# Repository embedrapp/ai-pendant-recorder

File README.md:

# AI Pendant Recorder

An open-source, privacy-first wearable audio recorder built around the Seeed XIAO ESP32S3. It records PDM microphone audio to removable microSD storage and uses a 5 × 5 RGB matrix for low-power status feedback.

## Hardware

- Seeed XIAO ESP32S3 **113991114** controller
- Infineon IM69D130 PDM microphone
- Molex 104031-0811 microSD socket
- MAX17048 fuel gauge and BMI270 IMU
- Regulated haptic output
- 25 × WS2812C-2020-V1 RGB LEDs
- Protected 500 mAh 1S LiPo design target
- No camera or speaker

## Schematics

The schematic is generated from [`pcb/ai_pendant_recorder.zen`](pcb/ai_pendant_recorder.zen) and is organized into battery/fuel-gauge, controller, motion, microphone, storage, haptics, LED power, and LED-row sections. Open the image for the full-resolution view.

## Board

The current four-layer KiCad board is in [`pcb/layout/layout.kicad_pcb`](pcb/layout/layout.kicad_pcb). It has a closed 36 × 76 mm rounded outline, four mounting holes, 115 footprints, 1,264 track segments, 200 vias, and no reported airwires.

Fresh checks on the current board:

| Check | Result |
|---|---|
| Zener source build | Pass — 115 components |
| ERC | Pass — 0 errors, 0 warnings, 79 style advice |
| KiCad DRC | **1 error**, 115 footprint-library configuration warnings |
| PDK-backed DFM | Pass — 0 findings |
| Firmware clean build | Pass for `seeed_xiao_esp32s3` |
| Enclosure CAD build | Pass — 16 valid solids |

The remaining DRC error is a 0.21 mm clearance between the IM69D130 acoustic opening and its surrounding ground pad, below the board-wide 0.25 mm hole-clearance rule. The geometry follows Infineon's recommended 0.8 mm sound port and SMD ground-pad land pattern, but the exception still needs an explicit KiCad rule or footprint-level resolution before the PCB checks are fully clean. The library warnings are caused by the standalone KiCad checker not loading the project-managed footprint libraries; they are not geometry violations.

## Mechanical design

### Pendant enclosure

The parametric enclosure includes a rounded two-part shell, front optical area,
record-button opening, side controls/access, and lanyard loop. The latest STEP
build contains 16 valid solids and measures 40 × 87.785 × 18.2 mm overall,
including the loop.

### Populated PCB model

The populated-board model is used to coordinate PCB and enclosure geometry.
Some component models and exact interface heights remain incomplete, so the
render is a design aid rather than proof of interference-free physical fit.

## Firmware

The Arduino/PlatformIO firmware currently provides:

- push-to-toggle 16-bit PDM audio capture;
- chunked WAV recording to FAT32 microSD;
- recovery of interrupted `.part` recordings at startup; and
- conservative idle/recording animations on the RGB matrix.

Wi-Fi upload, fuel-gauge monitoring, motor activation, and automatic file deletion are not implemented.

### Build

1. Install [PlatformIO](https://platformio.org/).
2. Clone this repository and enter it.
3. Build the default environment:

   ```sh
   pio run
   ```

4. Connect a Seeed XIAO ESP32S3 and upload:

   ```sh
   pio run --target upload
   pio device monitor --baud 115200
   ```

Use a qualified FAT32 microSD card. Hardware pin assignments are documented in [`docs/current-design.md`](docs/current-design.md); setup notes are in [`docs/setup.md`](docs/setup.md).

## Repository map

| Path | Purpose |
|---|---|
| `src/main.cpp` | Recorder firmware entry point |
| `include/` | Shared firmware configuration and WAV helpers |
| `tests/` | Host-side audio-format test |
| `pcb/ai_pendant_recorder.zen` | Electrical and connectivity source |
| `pcb/layout/` | Current KiCad PCB and schematic |
| `pcb/bom.json` | Structured generated BOM |
| `docs/bom.md` | Human-readable procurement notes |
| `mechanical/` | Parametric enclosure source and current PCB STEP import |

## Engineering status

The current source, PCB, firmware, and enclosure generators are maintained together and were freshly built or checked. Remaining hardware work is tracked in [`docs/current-design.md`](docs/current-design.md), including the microphone DRC rule, power and charging validation, exact motor selection, enclosure interface dimensions, and physical bench testing.

## Contributing

Issues and pull requests are welcome. Keep changes focused, identify the hardware revision they target, and include validation evidence where practical. Do not commit credentials, private recordings, generated build directories, or unreviewed manufacturing outputs.

## License

This project is intended to be open source, but no license file is currently present. Until the maintainers add one, copyright law reserves reuse rights; please open an issue before redistributing or incorporating the design.

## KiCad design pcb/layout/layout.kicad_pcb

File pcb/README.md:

# Electronics workspace

The maintained electrical source is `ai_pendant_recorder.zen`; the current physical board is `layout/layout.kicad_pcb`.

Sourcing metadata is stored in the source `PURCHASE_LINKS` / `DATASHEET_INDEX` maps and the persisted `bom.json` overlay. `bom.csv` is generated and should not be hand-edited.

## Board

- 36 × 76 mm rounded outline
- four copper layers, modeled at 1.62 mm total thickness
- 115 footprints
- 1,264 track segments and 200 vias
- no zones and no reported airwires

The source `Board(...)` points to `layout`, so there is one active board location. Regenerating or synchronizing a routed PCB is a deliberate board mutation; preserve and compare copper before doing so.

## Current checks

- Source build: pass, 115 components.
- ERC: pass, 79 style advice entries.
- DRC: one IM69D130 acoustic-hole/ground-land clearance error plus footprint-library configuration warnings.
- PDK-backed DFM: pass with no findings.

The microphone geometry follows Infineon's recommended 0.8 mm PCB sound port and surrounding solder-mask-defined ground land. Represent that intended geometry with a local KiCad rule or reviewed footprint change; do not weaken the global hole-clearance rule.

The four-layer stackup is a project model rather than a controlled-impedance fabricator stackup. Review boost current loops, trace widths, return paths, and the absence of copper planes before fabrication.

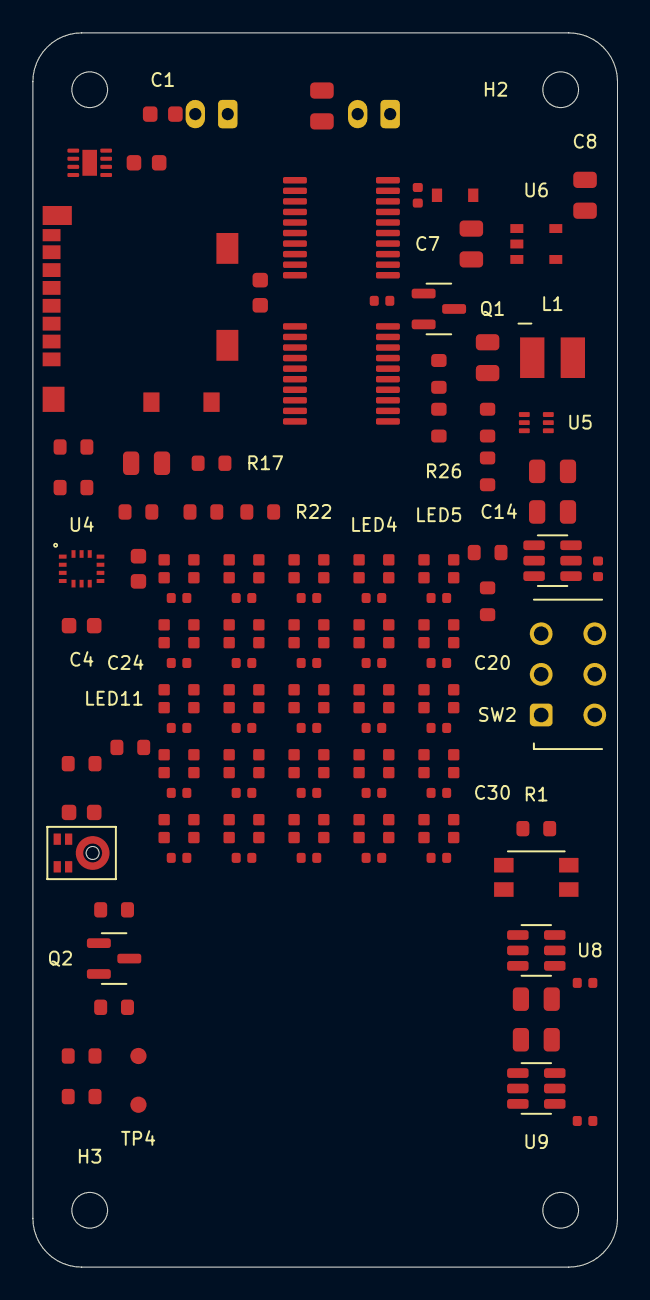
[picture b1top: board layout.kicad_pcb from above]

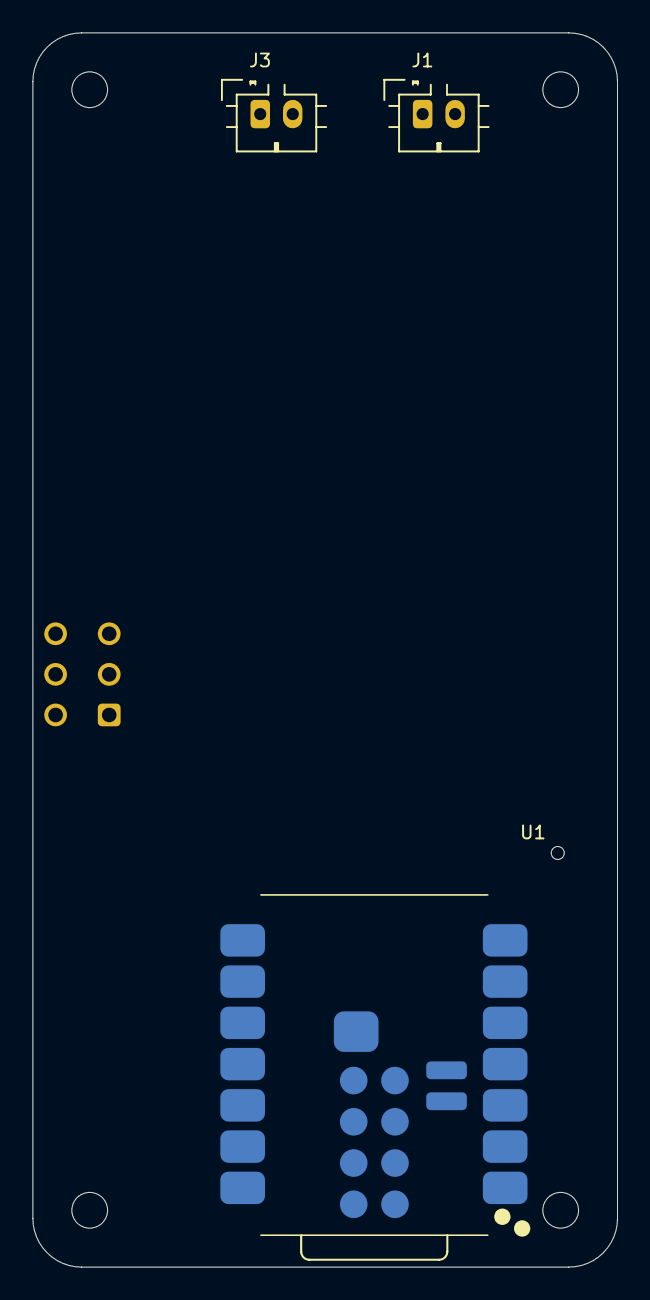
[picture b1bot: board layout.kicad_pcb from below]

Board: 2 copper layers, 36.0 x 76.0 mm, 115 parts (3 on the bottom side), 72 nets, no tracks yet.

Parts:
C1, C3, C4, C5, C9, C10: GCM188R71H104KA57J; C_0603_1608Metric
C2, C7, C8, C11, C12, C43, C44: CC0805KRX5R8BB106; C_0805_2012Metric
C13, C14: GRM21BR61A226ME44L; C_0805_2012Metric
C15, C16, C17, C18, C19, C20, C21, C22, C23, C24, C25, C26, C27, C28, C29, C30, C31, C32, C33, C34, C35, C36, C37, C38, C39, C45, C46: GRM155R71C104KA88D; C_0402_1005Metric
C40, C41, C42: GRM1555C1E102JA01D; C_0402_1005Metric
D1: NSVR0320MW2T1G; NSVR0320
H1, H2, H3, H4: M2 DIN965 Mechanical; MountingHole_2.2mm_M2_DIN965
J1, J3: B2B-PH-K-S; JST_PH_B2B-PH-K_1x02_P2.00mm_Vertical
J4: 104031-0811; Molex_104031-0811
L1: XEL4030-102MEC; XEL4030_102MEC
LED1, LED2, LED3, LED4, LED5, LED6, LED7, LED8, LED9, LED10, LED11, LED12, LED13, LED14, LED15, LED16, LED17, LED18, LED19, LED20, LED21, LED22, LED23, LED24, LED25: WS2812C-2020-V1; WS2812C_2020_V1
MK1: IM69D130V01XTSA1; IM69D130
Q1, Q2: AO3400A; SOT-23
R1, R8, R23, R26, R27, R29: RC0603FR-07100KL; R_0603_1608Metric
R4, R5, R30: RC0603FR-074K7L; R_0603_1608Metric
R7: RC0603FR-07100RL; R_0603_1608Metric
R16, R17: RC0603FR-0733RL; R_0603_1608Metric
R18, R19, R20, R21, R22: RC0603FR-0747KL; R_0603_1608Metric
R25: RC0603FR-07732KL; R_0603_1608Metric
R28: RC0603FR-07470RL; R_0603_1608Metric
SW1: PTS841GKSMTR LFS; PTS841GK
SW2: JS202011AQN; SW_CK_JS202011AQN_DPDT_Angled
TP3, TP4: ?; TestPoint_Pad_D1.0mm
U1: 113991114; XIAO
U3: MAX17048G+T10; kicad_footprint
U4: BMI270
U5: TPS61023DRLR; Texas_R-PDSO-N6_DRL-6
U6: AP2112K-3.3TRG1; AP2112K_3V3
U7, U8, U9: TPS22918DBVR; SOT-23-6
U10, U11: SN74CBTLV3245APWR; TSSOP-20

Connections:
BAT_RISE: C42.1, U9.4
BOOST_5V: C13.1, C14.1, R25.1, U5.6, U7.1
FG_SCL: R5.1, TP4.1, U3.7, U4.13, U10.11
FG_SDA: R4.1, TP3.1, U3.8, U4.14, U10.12
GND: C1.2, C2.2, C3.2, C4.2, C5.2, C7.2, C8.2, C9.2, C10.2, C11.2, C12.2, C13.2, C14.2, C15.2, C16.2, C17.2, C18.2, C19.2, C20.2, C21.2, C22.2, C23.2, C24.2, C25.2, C26.2, C27.2, C28.2, C29.2, C30.2, C31.2, C32.2, C33.2, C34.2, C35.2, C36.2, C37.2, C38.2, C39.2, C40.2, C41.2, C42.2, C43.2, C44.2, C45.2, C46.2, J1.2, J4.6, J4.11, LED1.2, LED2.2, LED3.2, LED4.2, LED5.2, LED6.2, LED7.2, LED8.2, LED9.2, LED10.2, LED11.2, LED12.2, LED13.2, LED14.2, LED15.2, LED16.2, LED17.2, LED18.2, LED19.2, LED20.2, LED21.2, LED22.2, LED23.2, LED24.2, LED25.2, MK1.4, MK1.5, Q1.2, Q2.2, R8.2, R23.2, R26.2, R27.2, R29.2, SW1.3, SW1.4, SW2.1, SW2.4, U1.13, U1.18, U1.24, U3.1, U3.4, U3.6, U3.9, U4.1, U4.6, U4.7, U5.4, U6.2, U7.2, U8.2, U9.2, U10.10, U11.6, U11.7, U11.8, U11.9, U11.10
HAPTIC_DRIVE: R7.1, U11.15
HOST_HAPTIC: U1.1, U11.5
HOST_IMU_INT: U1.16, U11.2
HOST_LED_DATA: U1.4, U11.4
HOST_LED_ENABLE: U1.3, U11.3
HOST_PDM_CLK: U1.19, U10.6
HOST_PDM_DATA: U1.15, U10.7
HOST_SCL: U1.6, U10.9
HOST_SDA: U1.5, U10.8
HOST_SD_CLK: U1.9, U10.2
HOST_SD_CS: U1.20, U10.3
HOST_SD_MISO: U1.10, U10.5
HOST_SD_MOSI: U1.11, U10.4
IMU_INT: U4.4, U11.18
ISOLATE_N: Q2.3, R30.1, U10.19, U11.19
LED_5V: C15.1, C16.1, C17.1, C18.1, C19.1, C20.1, C21.1, C22.1, C23.1, C24.1, C25.1, C26.1, C27.1, C28.1, C29.1, C30.1, C31.1, C32.1, C33.1, C34.1, C35.1, C36.1, C37.1, C38.1, C39.1, LED1.4, LED2.4, LED3.4, LED4.4, LED5.4, LED6.4, LED7.4, LED8.4, LED9.4, LED10.4, LED11.4, LED12.4, LED13.4, LED14.4, LED15.4, LED16.4, LED17.4, LED18.4, LED19.4, LED20.4, LED21.4, LED22.4, LED23.4, LED24.4, LED25.4, U7.5, U7.6
LED_CHAIN_1: LED1.1, LED2.3
LED_CHAIN_2: LED2.1, LED3.3
LED_CHAIN_3: LED3.1, LED4.3
LED_CHAIN_4: LED4.1, LED5.3
LED_CHAIN_5: LED5.1, LED6.3
LED_CHAIN_6: LED6.1, LED7.3
LED_CHAIN_7: LED7.1, LED8.3
LED_CHAIN_8: LED8.1, LED9.3
LED_CHAIN_9: LED9.1, LED10.3
LED_CHAIN_10: LED10.1, LED11.3
LED_CHAIN_11: LED11.1, LED12.3
LED_CHAIN_12: LED12.1, LED13.3
LED_CHAIN_13: LED13.1, LED14.3
LED_CHAIN_14: LED14.1, LED15.3
LED_CHAIN_15: LED15.1, LED16.3
LED_CHAIN_16: LED16.1, LED17.3
LED_CHAIN_17: LED17.1, LED18.3
LED_CHAIN_18: LED18.1, LED19.3
LED_CHAIN_19: LED19.1, LED20.3
LED_CHAIN_20: LED20.1, LED21.3
LED_CHAIN_21: LED21.1, LED22.3
LED_CHAIN_22: LED22.1, LED23.3
LED_CHAIN_23: LED23.1, LED24.3
LED_CHAIN_24: LED24.1, LED25.3
LED_DATA: LED1.3, R28.2
LED_DATA_MCU: R28.1, U11.16
LED_ENABLE: R27.1, U5.2, U7.3, U11.17
LED_FB: R25.2, R26.1, U5.1
LED_RISE: C40.1, U7.4
LED_SW: L1.2, U5.5
MCU_EN: SW2.2, U1.17
MOTOR_3V3: C8.1, D1.1, J3.1, U6.5
MOTOR_GATE: Q1.1, R7.2, R8.1
MOTOR_N: D1.2, J3.2, Q1.3
PDM_CLK: MK1.3, R16.2, R23.1
PDM_CLK_MCU: R16.1, U10.14
PDM_DATA: MK1.1, U10.13
PERIPH_RISE: C41.1, U8.4
RECORD_BUTTON: R1.1, SW1.1, SW1.2, U1.2
RUN_ENABLE: Q2.1, R29.1, SW2.5, U8.3, U9.3
SD_CLK: J4.5, R17.2
SD_CLK_MCU: R17.1, U10.18
SD_CS: J4.2, R18.1, U10.17
SD_DAT1: J4.8, R21.1
SD_DAT2: J4.1, R22.1
SD_MISO: J4.7, R20.1, U10.15
SD_MOSI: J4.3, R19.1, U10.16
V3V3: C4.1, C5.1, C9.1, C10.1, C11.1, C45.1, C46.1, J4.4, MK1.2, R4.2, R5.2, R18.2, R19.2, R20.2, R21.2, R22.2, R30.2, U4.5, U4.8, U4.12, U8.5, U8.6, U10.20, U11.20
V3V3_AON: C43.1, R1.2, SW2.6, U1.12, U8.1
VBAT: C1.1, C2.1, C3.1, C44.1, J1.1, U1.23, U3.2, U3.3, U9.1
VBAT_PERIPH: C7.1, C12.1, L1.1, U5.3, U6.1, U6.3, U9.5, U9.6

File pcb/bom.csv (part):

Quantity,References,Populate,Value,Package,Mount,Manufacturer,MPN,Supplier,Supplier Part Number,Alternatives,Description,Datasheet,Configuration,Zener Paths,Source URL,Currency,Unit Price,Extended Price,Stock,Availability,Sourcing Updated
6,C1 C3 C4 C5 C9 C10,Yes,100nF 50V X7R,0603,,Murata,GCM188R71H104KA57J,,,,100nF 50V X7R,,Configured,ai_pendant_recorder.zen:<root>.C1.C | ai_pendant_recorder.zen:<root>.C3.C | ai_pendant_recorder.zen:<root>.C4.C | ai_pendant_recorder.zen:<root>.C5.C | ai_pendant_recorder.zen:<root>.C9.C | ai_pendant_recorder.zen:<root>.C10.C,https://www.digikey.in/en/products/detail/murata-electronics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,,,,,,
7,C2 C7 C8 C11 C12 C43 C44,Yes,10uF 25V X5R,0805,,YAGEO,CC0805KRX5R8BB106,,,,10uF 25V X5R,,Configured,ai_pendant_recorder.zen:<root>.C2.C | ai_pendant_recorder.zen:<root>.C7.C | ai_pendant_recorder.zen:<root>.C8.C | ai_pendant_recorder.zen:<root>.C11.C | ai_pendant_recorder.zen:<root>.C12.C | ai_pendant_recorder.zen:<root>.C43.C | ai_pendant_recorder.zen:<root>.C44.C,https://www.mouser.in/en/ProductDetail/YAGEO/CC0805KRX5R8BB1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,,,,,,
2,C13 C14,Yes,22uF 10V X5R,0805,,Murata,GRM21BR61A226ME44L,,,,22uF 10V X5R,,Configured,ai_pendant_recorder.zen:<root>.C13.C | ai_pendant_recorder.zen:<root>.C14.C,https://www.mouser.in/en/ProductDetail/Murata-Electronics/GR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,,,,,,
27,C15 C16 C17 C18 C19 C20 C21 C22 C23 C24 C25 C26 C27 C28 C29 C30 C31 C32 C33 C34 C35 C36 C37 C38 C39 C45 C46,Yes,100nF 16V X7R,0402,,Murata,GRM155R71C104KA88D,element14,4326785,,100nF 16V X7R,,Configured,ai_pendant_recorder.zen:<root>.C15.C | ai_pendant_recorder.zen:<root>.C16.C | ai_pendant_recorder.zen:<root>.C17.C | ai_pendant_recorder.zen:<root>.C18.C | ai_pendant_recorder.zen:<root>.C19.C | ai_pendant_recorder.zen:<root>.C20.C | ai_pendant_recorder.zen:<root>.C21.C | ai_pendant_recorder.zen:<root>.C22.C | ai_pendant_recorder.zen:<root>.C23.C | ai_pendant_recorder.zen:<root>.C24.C | ai_pendant_recorder.zen:<root>.C25.C | ai_pendant_recorder.zen:<root>.C26.C | ai_pendant_recorder.zen:<root>.C27.C | ai_pendant_recorder.zen:<root>.C28.C | ai_pendant_recorder.zen:<root>.C29.C | ai_pendant_recorder.zen:<root>.C30.C | ai_pendant_recorder.zen:<root>.C31.C | ai_pendant_recorder.zen:<root>.C32.C | ai_pendant_recorder.zen:<root>.C33.C | ai_pendant_recorder.zen:<root>.C34.C | ai_pendant_recorder.zen:<root>.C35.C | ai_pendant_recorder.zen:<root>.C36.C | ai_pendant_recorder.zen:<root>.C37.C | ai_pendant_recorder.zen:<root>.C38.C | ai_pendant_recorder.zen:<root>.C39.C | ai_pendant_recorder.zen:<root>.C45.C | ai_pendant_recorder.zen:<root>.C46.C,https://in.element14.com/murata/grm155r71c104ka88d/cap-mlcc-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,,,,,,
3,C40 C41 C42,Yes,1nF 25V C0G,0402,,Murata,GRM1555C1E102JA01D,,,,1nF 25V C0G,,Configured,ai_pendant_recorder.zen:<root>.C40.C | ai_pendant_recorder.zen:<root>.C41.C | ai_pendant_recorder.zen:<root>.C42.C,https://www.mouser.in/en/ProductDetail/Murata-Electronics/GR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,,,,,,
1,D1,Yes,,NSVR0320,,onsemi,NSVR0320MW2T1G,,,,,,Configured,ai_pendant_recorder.zen:<root>.D1.D,https://in.element14.com/on-semiconductor/nsvr0320mw2t1g/sch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,,,,,,
2,J1 J3,Yes,,JST_PH_B2B-PH-K_1x02_P2.00mm_Vertical,,"J.S.T. Mfg. Co., Ltd.",B2B-PH-K-S,DigiKey,455-1704-ND,,"JST PH series 2-position top-entry shrouded through-hole header, 2.00 mm pitch.",,Configured,ai_pendant_recorder.zen:<root>.J1.J_B2B_PH_K_S | ai_pendant_recorder.zen:<root>.J3.J_B2B_PH_K_S,https://www.digikey.in/en/products/detail/jst-sales-america-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,,,,,,
1,J4,Yes,,Molex_104031-0811,,Molex,104031-0811,,,,Active 1.42 mm push-pull microSD socket; front entry; normally-open card detect,https://www.molex.com/content/dam/molex/molex-dot-com/produc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,Configured,ai_pendant_recorder.zen:<root>.J4.SD,https://www.mouser.in/en/ProductDetail/Molex/104031-0811?qs=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,,,,,,
1,L1,Yes,,XEL4030_102MEC,,Coilcraft,XEL4030-102MEC,,,,"1 uH +/-20%, 9 A Isat, 9.78 mOhm max DCR shielded inductor",https://www.coilcraft.com/getmedia/8245f050-f190-4295-8c41-7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,Configured,ai_pendant_recorder.zen:<root>.L1.L,https://www.mouser.in/en/ProductDetail/Coilcraft/XEL4030-102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,,,,,,
25,LED1 LED2 LED3 LED4 LED5 LED6 LED7 LED8 LED9 LED10 LED11 LED12 LED13 LED14 LED15 LED16 LED17 LED18 LED19 LED20 LED21 LED22 LED23 LED24 LED25,Yes,,WS2812C_2020_V1,,Worldsemi,WS2812C-2020-V1,LCSC,C2976072,,"2.0 mm addressable RGB LED, 5 mA/channel, 3.7-5.3 V, LCSC C2976072",https://datasheet.lcsc.com/datasheet/pdf/09f4c697250f44092a0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,Configured,ai_pendant_recorder.zen:<root>.LED1.RGB | ai_pendant_recorder.zen:<root>.LED2.RGB | ai_pendant_recorder.zen:<root>.LED3.RGB | ai_pendant_recorder.zen:<root>.LED4.RGB | ai_pendant_recorder.zen:<root>.LED5.RGB | ai_pendant_recorder.zen:<root>.LED6.RGB | ai_pendant_recorder.zen:<root>.LED7.RGB | ai_pendant_recorder.zen:<root>.LED8.RGB | ai_pendant_recorder.zen:<root>.LED9.RGB | ai_pendant_recorder.zen:<root>.LED10.RGB | ai_pendant_recorder.zen:<root>.LED11.RGB | ai_pendant_recorder.zen:<root>.LED12.RGB | ai_pendant_recorder.zen:<root>.LED13.RGB | ai_pendant_recorder.zen:<root>.LED14.RGB | ai_pendant_recorder.zen:<root>.LED15.RGB | ai_pendant_recorder.zen:<root>.LED16.RGB | ai_pendant_recorder.zen:<root>.LED17.RGB | ai_pendant_recorder.zen:<root>.LED18.RGB | ai_pendant_recorder.zen:<root>.LED19.RGB | ai_pendant_recorder.zen:<root>.LED20.RGB | ai_pendant_recorder.zen:<root>.LED21.RGB | ai_pendant_recorder.zen:<root>.LED22.RGB | ai_pendant_recorder.zen:<root>.LED23.RGB | ai_pendant_recorder.zen:<root>.LED24.RGB | ai_pendant_recorder.zen:<root>.LED25.RGB,https://www.lcsc.com/product-detail/C2976072.html,,,,,,
1,MK1,Yes,,IM69D130,,Infineon,IM69D130V01XTSA1,element14,2986420,,Bottom-port PDM microphone; SELECT low; place 100nF at VDD and provide PCB acoustic opening,https://www.infineon.com/row/public/documents/24/49/infineon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,Configured,ai_pendant_recorder.zen:<root>.MK1.MIC,https://in.element14.com/infineon/im69d130v01xtsa1/mems-micr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,,,,,,
2,Q1 Q2,Yes,,SOT-23,,Alpha & Omega Semiconductor,AO3400A,,,,Alpha & Omega Semiconductor AO3400A 30 V N-channel MOSFET in SOT-23,https://www.aosmd.com/res/datasheets/AO3400A.pdf,Configured,ai_pendant_recorder.zen:<root>.Q1.Q_AO3400A | ai_pendant_recorder.zen:<root>.Q2.Q_AO3400A,https://www.digikey.in/en/products/detail/alpha-omega-semico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,,,,,,
6,R1 R8 R23 R26 R27 R29,Yes,100k 100mW,0603,,YAGEO,RC0603FR-07100KL,DigiKey,311-100KHRCT-ND,,100k 100mW,,Configured,ai_pendant_recorder.zen:<root>.R1.R | ai_pendant_recorder.zen:<root>.R8.R | ai_pendant_recorder.zen:<root>.R23.R | ai_pendant_recorder.zen:<root>.R26.R | ai_pendant_recorder.zen:<root>.R27.R | ai_pendant_recorder.zen:<root>.R29.R,https://www.digikey.in/en/products/detail/yageo/RC0603FR-071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,,,,,,
3,R4 R5 R30,Yes,4.7k 100mW,0603,,YAGEO,RC0603FR-074K7L,,,,4.7k 100mW,,Configured,ai_pendant_recorder.zen:<root>.R4.R | ai_pendant_recorder.zen:<root>.R5.R | ai_pendant_recorder.zen:<root>.R30.R,https://www.digikey.in/en/products/detail/yageo/RC0603FR-074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,,,,,,
1,R7,Yes,100 100mW,0603,,YAGEO,RC0603FR-07100RL,,,,100 100mW,,Configured,ai_pendant_recorder.zen:<root>.R7.R,https://www.digikey.in/en/products/detail/yageo/RC0603FR-071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,,,,,,
2,R16 R17,Yes,33 100mW,0603,,YAGEO,RC0603FR-0733RL,element14,9238301,,33 100mW,,Configured,ai_pendant_recorder.zen:<root>.R16.R | ai_pendant_recorder.zen:<root>.R17.R,https://in.element14.com/yageo/rc0603fr-0733rl/res-33r-1-0-1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,,,,,,
5,R18 R19 R20 R21 R22,Yes,47k 100mW,0603,,YAGEO,RC0603FR-0747KL,element14,9238689,,47k 100mW,,Configured,ai_pendant_recorder.zen:<root>.R18.R | ai_pendant_recorder.zen:<root>.R19.R | ai_pendant_recorder.zen:<root>.R20.R | ai_pendant_recorder.zen:<root>.R21.R | ai_pendant_recorder.zen:<root>.R22.R,https://in.element14.com/yageo/rc0603fr-0747kl/res-47k-1-0-1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,,,,,,
1,R25,Yes,732k 100mW,0603,,YAGEO,RC0603FR-07732KL,,,,732k 100mW,,Configured,ai_pendant_recorder.zen:<root>.R25.R,https://www.digikey.com/en/products/detail/yageo/RC0603FR-07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,,,,,,
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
